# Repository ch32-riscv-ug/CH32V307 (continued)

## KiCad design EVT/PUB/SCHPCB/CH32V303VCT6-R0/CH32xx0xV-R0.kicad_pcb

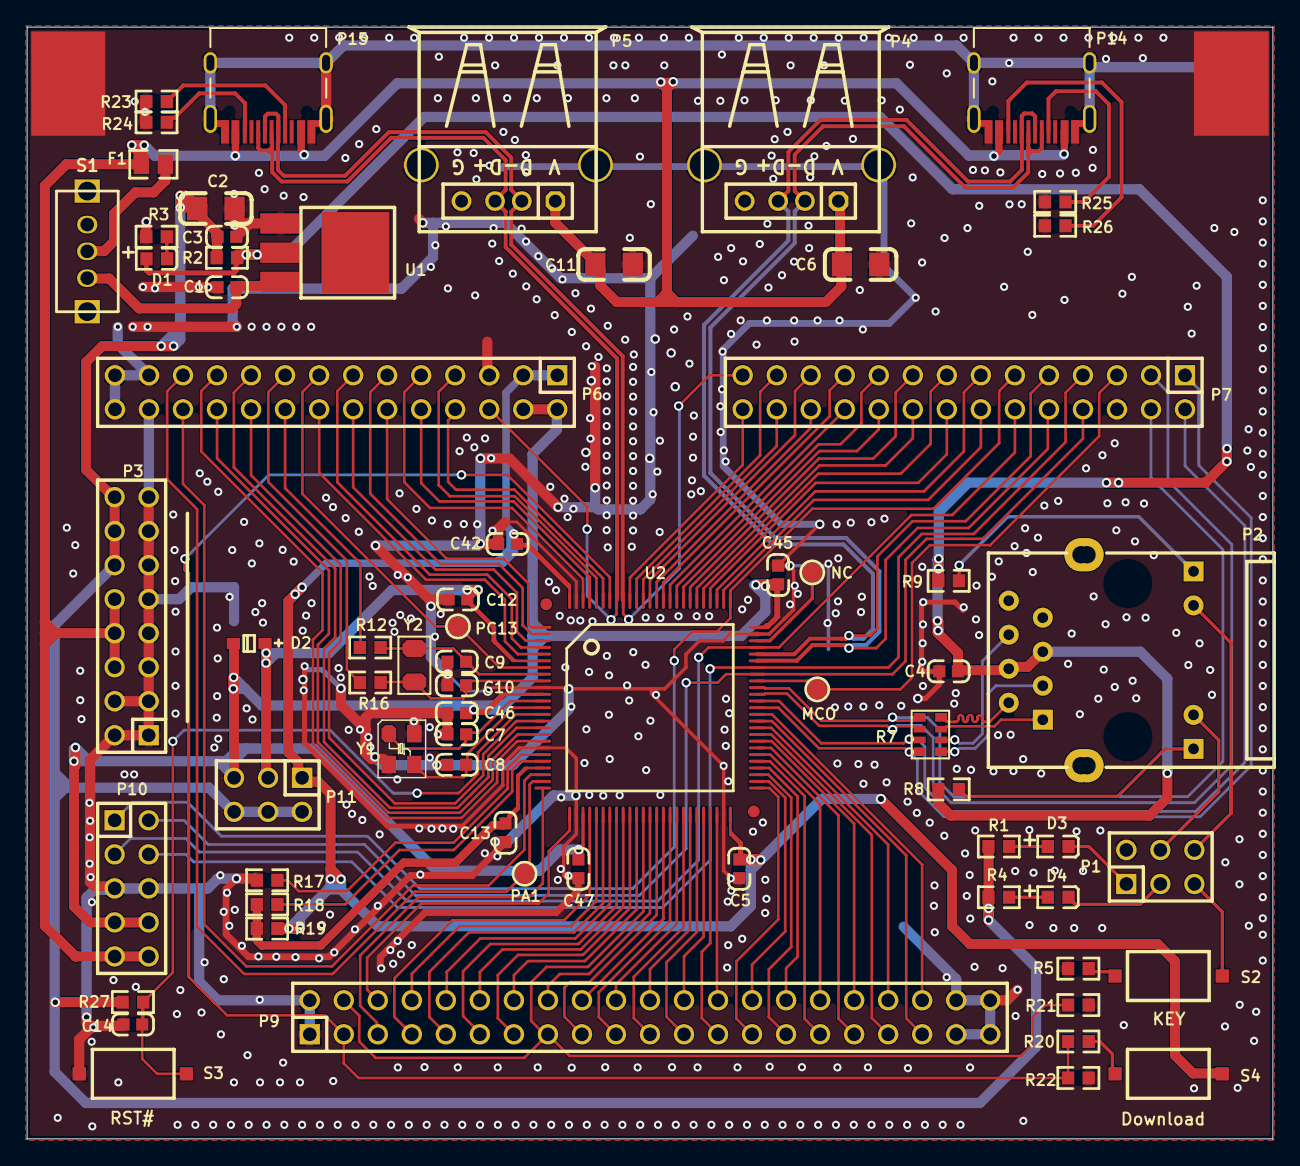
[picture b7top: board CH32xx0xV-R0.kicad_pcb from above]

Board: 2 copper layers, 93.0 x 83.0 mm, 68 parts (0 on the bottom side), 119 nets.

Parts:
C1, C3, C5, C12, C13, C14, C42, C45, C46, C47: 0.1uF; 0603_C
C2, C6, C11: 10uF; 3216_C
C4: 1uF; 0603_C
C7, C8: 22pF; 0603_C
C9, C10: 12pF; 0603_C
D1, D4: RED; 0603+
D2: B0520WS; SOD-323
D3: BLUE; 0603+
F1: 500mA; 0805
MCO: Testpoint; TESTPOINT1
NC: Testpoint; TESTPOINT1
P1: IO; IDC6-2.54mm
P2: HR911105A
P3: HEADER 8x2; IDC16-2.54mm
P4: USBFS; USBAF
P5: USBHS; USBAF
P6, P7: HEADER 14x2; IDC28-2.54MM
P9: HEADER 21x2; IDC42-2.54MM
P10: LINK; IDC10-2.54mm
P11: HEADER 3x2; IDC6-2.54mm
P14: USBFS; TYPE-C-Receptacle-2.0
P15: USBHS; TYPE-C-Receptacle-2.0
PA1: Testpoint; TESTPOINT1
PC13: Testpoint; TESTPOINT1
R1, R3, R4, R8, R9, R20: 1K; 0603
R2, R17, R18, R19: 0R; 0603
R5, R21, R22, R27: 10K; 0603
R7: 0Ω; RCA-8P4R-0603
R12, R16: NC(0R); 0603
R23: NC(5.1K); 0603
R24, R25, R26: 5.1K; 0603
S1: SW SPDT; KEY2
S2: KEY; SMD_6.1x3.65x2.5mm-KEY
S3: RST#; SMD_6.1x3.65x2.5mm-KEY
S4: Download; SMD_6.1x3.65x2.5mm-KEY
U1: 1117-3.3V; SOT-223
U2: CH32F207V; LQFP100
Y1: 8MHz; XT3225
Y2: 32768Hz; FC-135

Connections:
3V3: C2.1, C3.1, P3.12, P3.14, P3.16, P11.2, P11.4, P11.6, R1.1, R2.1, R4.1, R27.2
3V3S: C4.2, D1.1, P2.4, P2.5, R2.2, R8.1, R9.1, U1.2
5V: C6.1, C11.1, F1.1, P3.6, P3.8, P3.10, P4.1, P5.1, P10.9, P10.10, P14.A4, P14.B4, P15.A4, P15.B4
BOOT0: P9.3, R20.1, R22.1, U2.94
BOOT1: P9.4, P9.15, R21.1, U2.37
ELED1: P1.4, P2.10
ELED2: P1.6, P2.11
ERXN: P7.2, R7.3, U2.64
ERXN1: P2.6, R7.6
ERXP: P7.1, R7.4, U2.63
ERXP1: P2.3, R7.5
ETXN: P7.4, R7.1, U2.66
ETXN1: P2.2, R7.8
ETXP: P7.3, R7.2, U2.65
ETXP1: P2.1, R7.7
GND: C1.2, C2.2, C3.2, C4.1, C5.2, C6.2, C7.1, C8.1, C9.1, C10.1, C11.2, C12.1, C13.2, C14.1, C42.1, C45.2, C46.2, C47.1, P1.2, P2.8, P3.1, P3.2, P3.3, P3.4, P3.5, P3.7, P3.9, P3.11, P3.13, P3.15, P4.0, P4.4, P5.0, P5.4, P6.5, P6.25, P6.26, P6.27, P6.28, P7.6, P9.1, P9.2, P9.39, P9.40, P9.41, P9.42, P10.5, P10.6, P14.0, P14.A1, P14.B1, P15.0, P15.A1, P15.B1, R3.2, R5.1, R17.1, R21.2, R22.2, R23.2, R24.2, R25.2, R26.2, S3.1, U1.1, U2.10, U2.19, U2.27, U2.49, U2.74, U2.99, Y1.2, Y1.4
KEY: P1.5, S2.1
LED1: D3.2, P1.1
LED2: D4.2, P1.3
MCO: MCO.1, P7.5, U2.67
NC: NC.1, U2.73
NRST: C14.2, R27.1, S3.2, U2.14
NetC1_1: C1.1, S1.2, U1.3
NetD1_2: D1.2, R3.1
NetD3_1: D3.1, R1.2
NetD4_1: D4.1, R4.2
NetF1_2: F1.2, S1.1
NetP2_9: P2.9, R8.2
NetP2_12: P2.12, R9.2
NetP14_A5: P14.A5, R25.1
NetP14_B5: P14.B5, R26.1
NetP15_A5: P15.A5, R23.1
NetP15_B5: P15.B5, R24.1
NetR5_2: R5.2, S2.2
NetR20_2: R20.2, S4.2
PA0: P6.24, U2.23
PA1: P6.23, PA1.1, U2.24
PA2: P9.5, U2.25
PA3: P9.6, U2.26
PA4: P9.7, U2.29
PA5: P9.8, U2.30
PA6: P9.9, U2.31
PA7: P9.10, U2.32
PA9: P7.8, P10.2, U2.68
PA10: P7.7, P10.4, U2.69
PA11: P4.2, P7.10, P14.A7, P14.B7, U2.70
PA12: P4.3, P7.9, P14.A6, P14.B6, U2.71
PA13: P7.12, P10.3, U2.72
PA14: P7.11, P10.1, U2.76
PA15: P7.14, U2.77
PB0: P9.13, U2.35
PB1: P9.14, U2.36
PB3: P7.26, U2.89
PB4: P7.25, U2.90
PB5: P7.28, U2.91
PB6: P5.2, P7.27, P15.A7, P15.B7, U2.92
PB7: P5.3, P6.6, P15.A6, P15.B6, U2.93
PB8: P6.8, U2.95
PB9: P6.7, U2.96
PB10: P9.25, U2.47
PB11: P9.26, U2.48
PB12: P9.27, U2.51
PB13: P9.28, U2.52
PB14: P9.29, U2.53
PB15: P9.30, U2.54
PC0: P6.20, U2.15
PC1: P6.19, U2.16
PC2: P6.22, U2.17
PC3: P6.21, U2.18
PC4: P9.11, U2.33
PC5: P9.12, U2.34
PC10: P7.13, U2.78
PC11: P7.16, U2.79
PC12: P7.15, U2.80
PC13: P6.15, PC13.1, U2.7
PC14: P6.18, R12.1
PC15: P6.17, R16.1
PD0: P7.18, U2.81
PD1: P7.17, U2.82
PD2: P7.20, U2.83
PD3: P7.19, U2.84
PD4: P7.22, U2.85
PD5: P7.21, U2.86
PD6: P7.24, U2.87
PD7: P7.23, U2.88
PD8: P9.31, U2.55
PD9: P9.32, U2.56
PD10: P9.33, U2.57
PD11: P9.34, U2.58
PD12: P9.35, U2.59
PD13: P9.36, U2.60
PD14: P9.37, U2.61
PD15: P9.38, U2.62
PE0: P6.10, U2.97
PE1: P6.9, U2.98
PE2: P6.12, U2.1
PE3: P6.11, U2.2
PE4: P6.14, U2.3
PE5: P6.13, U2.4
PE6: P6.16, U2.5
PE7: P9.16, U2.38
PE8: P9.17, U2.39
PE9: P9.18, U2.40
PE10: P9.19, U2.41
PE11: P9.20, U2.42
PE12: P9.21, U2.43
PE13: P9.22, U2.44
PE14: P9.23, U2.45
PE15: P9.24, U2.46
VBAT: C12.2, D2.1, P11.3, U2.6
VDD: C45.1, C46.1, C47.2, D2.2, P6.2, P6.4, P10.7, P10.8, P11.5, U2.11, U2.28, U2.75
VDDA: C13.1, R18.1, R19.2, U2.22
VIO: C5.1, C42.2, P6.1, P6.3, P11.1, R19.1, S4.1, U2.50, U2.100
VREF+: R18.2, U2.21
VREF-: R17.2, U2.20
X32KI: C9.2, R12.2, U2.8, Y2.1
X32KO: C10.2, R16.2, U2.9, Y2.2
XI: C7.2, U2.12, Y1.1
XO: C8.2, U2.13, Y1.3

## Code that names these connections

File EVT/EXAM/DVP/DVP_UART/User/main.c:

/********************************** (C) COPYRIGHT *******************************
* File Name          : main.c
* Author             : WCH
* Version            : V1.0.0
* Date               : 2024/03/05
* Description        : Main program body.
*********************************************************************************
* Copyright (c) 2021 Nanjing Qinheng Microelectronics Co., Ltd.
* Attention: This software (modified or not) and binary are used for 
* microcontroller manufactured by Nanjing Qinheng Microelectronics.
*******************************************************************************/
#include "debug.h"
#include "ov.h"

/*
 *@Note
  DVP routine to operate OV2640 camera JPEG mode:
    Output picture data through UART2 (PA2), display pictures through serial port image software,
    or take 0xFF from a frame of data, starting with 0xD8;0xFF, data at the end of 0xD9, modify the
    file format to display pictures.
  DVP--PIN:
    D10--PD6
    D11--PD2
    D8--PC10
    D9--PC12
    DPWDN--PC3
    DPCLK--PA6
    D7--PB9
    D6--PB8
    D5--PB6
    D4--PC11
    D3--PC9
    D2--PC8
    D1--PA10
    D0--PA9
    RESET--PC13
    SDA--PB11
    HERF--PA4
    SDCLK--PB10
    SYNC--PA5

    Use UART2 (PA2) serial port output, #define DEBUG DEBUG_UART2 in debug.h
    UART1(PA9) is occupied by DVP
 */


/* DVP Work Mode */
#define JPEG_MODE     1
/* DVP Work Mode Selection */
#define DVP_Work_Mode    JPEG_MODE


UINT32  JPEG_DVPDMAaddr0 = 0x20005000;
UINT32  JPEG_DVPDMAaddr1 = 0x20005000 + OV2640_JPEG_WIDTH;

UINT32  RGB565_DVPDMAaddr0 = 0x20005000;
UINT32  RGB565_DVPDMAaddr1 = 0x20005000 + RGB565_COL_NUM;

volatile UINT32 frame_cnt = 0;
volatile UINT32 addr_cnt = 0;
volatile UINT32 href_cnt = 0;

void DVP_IRQHandler (void) __attribute__((interrupt("WCH-Interrupt-fast")));

/*********************************************************************
 * @fn      UART2_Send_Byte
 *
 * @brief   UART2 send one byte data.
 *
 * @param   t - UART send Data.
 *
 * @return  none
 */
void UART2_Send_Byte(u8 t)
{
    while (USART_GetFlagStatus(USART2, USART_FLAG_TC) == RESET);
    USART_SendData(USART2, t);
}

/*********************************************************************
 * @fn      DVP_Init
 *
 * @brief   Init DVP
 *
 * @return  none
 */
void DVP_Init(void)
{
    NVIC_InitTypeDef NVIC_InitStructure={0};

    RCC_AHBPeriphClockCmd(RCC_AHBPeriph_DVP, ENABLE);

    DVP->CR0 &= ~RB_DVP_MSK_DAT_MOD;

#if (DVP_Work_Mode == JPEG_MODE)
    /* VSYNC��HSYNC - High level active */
    DVP->CR0 |= RB_DVP_D8_MOD | RB_DVP_V_POLAR | RB_DVP_JPEG;
    DVP->CR1 &= ~(RB_DVP_ALL_CLR| RB_DVP_RCV_CLR);

    DVP->COL_NUM = OV2640_JPEG_WIDTH;

    DVP->DMA_BUF0 = JPEG_DVPDMAaddr0;        //DMA addr0
    DVP->DMA_BUF1 = JPEG_DVPDMAaddr1;        //DMA addr1
#endif

    /* Set frame capture rate */
    DVP->CR1 &= ~RB_DVP_FCRC;
    DVP->CR1 |= DVP_RATE_25P;  //25%

    /* Interupt Enable */
    DVP->IER |= RB_DVP_IE_STP_FRM;
    DVP->IER |= RB_DVP_IE_FIFO_OV;
    DVP->IER |= RB_DVP_IE_FRM_DONE;
    DVP->IER |= RB_DVP_IE_ROW_DONE;
    DVP->IER |= RB_DVP_IE_STR_FRM;

    NVIC_InitStructure.NVIC_IRQChannel = DVP_IRQn;
    NVIC_InitStructure.NVIC_IRQChannelPreemptionPriority = 0;
    NVIC_InitStructure.NVIC_IRQChannelSubPriority = 0;
    NVIC_InitStructure.NVIC_IRQChannelCmd = ENABLE;
    NVIC_Init(&NVIC_InitStructure);

    DVP->CR1 |= RB_DVP_DMA_EN;  //enable DMA
    DVP->CR0 |= RB_DVP_ENABLE;  //enable DVP
}

u32 DVP_ROW_cnt=0;

/*********************************************************************
 * @fn      DVP_IRQHandler
 *
 * @brief   This function handles DVP exception.
 *
 * @return  none
 */
void DVP_IRQHandler(void)
{
    if (DVP->IFR & RB_DVP_IF_ROW_DONE)
    {
        /* Write 0 clear 0 */
        DVP->IFR &= ~RB_DVP_IF_ROW_DONE;  //clear Interrupt

#if (DVP_Work_Mode == JPEG_MODE)
        href_cnt++;

        if (addr_cnt%2)     //buf1 done
        {
            addr_cnt++;
            DVP->DMA_BUF1 += OV2640_JPEG_WIDTH *2;
        }
        else                //buf0 done
        {
            addr_cnt++;
            DVP->DMA_BUF0 += OV2640_JPEG_WIDTH *2;
        }

#endif

    }

    if (DVP->IFR & RB_DVP_IF_FRM_DONE)
    {
        DVP->IFR &= ~RB_DVP_IF_FRM_DONE;  //clear Interrupt

#if (DVP_Work_Mode == JPEG_MODE)
        DVP->CR0 &= ~RB_DVP_ENABLE;       //disable DVP

        /* Use uart2 send JPEG data */
        {
            UINT32 i;
            UINT8 val;

            href_cnt = href_cnt*OV2640_JPEG_WIDTH;

            for(i=0; i<href_cnt; i++){
                val = *(UINT8*)(0x20005000+i);
                UART2_Send_Byte(val);
            }
        }

        DVP->CR0 |= RB_DVP_ENABLE;  //enable DVP

        DVP->DMA_BUF0 = JPEG_DVPDMAaddr0;        //DMA addr0
        DVP->DMA_BUF1 = JPEG_DVPDMAaddr1;        //DMA addr1
        href_cnt = 0;

        addr_cnt =0;

#endif

    }

    if (DVP->IFR & RB_DVP_IF_STR_FRM)
    {
        DVP->IFR &= ~RB_DVP_IF_STR_FRM;  //clear Interrupt

        frame_cnt++;
    }

    if (DVP->IFR & RB_DVP_IF_STP_FRM)
    {
        DVP->IFR &= ~RB_DVP_IF_STP_FRM;  //clear Interrupt

    }

    if (DVP->IFR & RB_DVP_IF_FIFO_OV)
    {
        DVP->IFR &= ~RB_DVP_IF_FIFO_OV;   //clear Interrupt

#if 0
        printf("FIFO OV\r\n");

#endif
    }

}

/*********************************************************************
 * @fn      main
 *
 * @brief   Main program.
 *
 * @return  none
 */
int main(void)
{
    NVIC_PriorityGroupConfig(NVIC_PriorityGroup_2);
	SystemCoreClockUpdate();
	Delay_Init();
	USART_Printf_Init(921600);	
	printf("SystemClk:%d\r\n",SystemCoreClock);
	printf( "ChipID:%08x\r\n", DBGMCU_GetCHIPID() );
    while(OV2640_Init())
    {
        printf("Camera Model Err\r\n");
        Delay_Ms(1000);
    }

    Delay_Ms(1000);

    RGB565_Mode_Init();
    Delay_Ms(1000);

#if (DVP_Work_Mode == JPEG_MODE)
    printf("JPEG_MODE\r\n");
    JPEG_Mode_Init();
    Delay_Ms(1000);

#endif

    DVP_Init();

    while(1);
}

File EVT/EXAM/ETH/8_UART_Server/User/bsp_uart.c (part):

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 *
 *  @brief   initialize uart1~uart8 io
 *
 *           UART1  TX-->PA9   RX-->PA10
 *           UART2  TX-->PA2   RX-->PA3
 *           UART3  TX-->PB10  RX-->PB11
 *           UART4  TX-->PC10  RX-->PC11
 *           UART5  TX-->PC12  RX-->PD2
 *           UART6  TX-->PC0   RX-->PC1   |  TX_2-->PE10   RX_2-->PE11
 *           UART7  TX-->PC2   RX-->PC3
 *           UART8  TX-->PC4   RX-->PC5
 *
 *  @param   none
 *
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    		               RCC_APB2Periph_GPIOC|RCC_APB2Periph_GPIOD|RCC_APB2Periph_GPIOE, ENABLE);

#ifndef CH32V307_DEBUG
    /* UART1 TX-->PA9   RX-->PA10 */
	GPIO_InitStructure.GPIO_Pin = GPIO_Pin_9;
	GPIO_InitStructure.GPIO_Speed = GPIO_Speed_50MHz;
	GPIO_InitStructure.GPIO_Mode = GPIO_Mode_AF_PP;
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	GPIO_Init(GPIOA, &GPIO_InitStructure);
#endif

    /* UART2 TX-->PA2   RX-->PA3 */
    GPIO_InitStructure.GPIO_Pin = GPIO_Pin_2;
    GPIO_InitStructure.GPIO_Speed = GPIO_Speed_50MHz;
    GPIO_InitStructure.GPIO_Mode = GPIO_Mode_AF_PP;
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    GPIO_Init(GPIOA, &GPIO_InitStructure);


    /* UART3 TX-->PB10  RX-->PB11 */
	GPIO_InitStructure.GPIO_Pin = GPIO_Pin_10;
	GPIO_InitStructure.GPIO_Speed = GPIO_Speed_50MHz;
	GPIO_InitStructure.GPIO_Mode = GPIO_Mode_AF_PP;
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	GPIO_InitStructure.GPIO_Mode = GPIO_Mode_IN_FLOATING;
	GPIO_Init(GPIOB, &GPIO_InitStructure);

	/* UART4 TX-->PC10  RX-->PC11 */
	GPIO_InitStructure.GPIO_Pin = GPIO_Pin_10;
	GPIO_InitStructure.GPIO_Speed = GPIO_Speed_50MHz;
	GPIO_InitStructure.GPIO_Mode = GPIO_Mode_AF_PP;
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	GPIO_InitStructure.GPIO_Mode = GPIO_Mode_IN_FLOATING;
	GPIO_Init(GPIOC, &GPIO_InitStructure);

	/* UART5 TX-->PC12  RX-->PD2 */
	GPIO_InitStructure.GPIO_Pin = GPIO_Pin_12;
	GPIO_InitStructure.GPIO_Speed = GPIO_Speed_50MHz;
	GPIO_InitStructure.GPIO_Mode = GPIO_Mode_AF_PP;
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	GPIO_InitStructure.GPIO_Mode = GPIO_Mode_IN_FLOATING;
	GPIO_Init(GPIOD, &GPIO_InitStructure);

	/* UART6 TX-->PC0  RX-->PC1  |  TX_2-->PE10   RX_2-->PE11 */
//	GPIO_InitStructure.GPIO_Pin = GPIO_Pin_0;
//	GPIO_InitStructure.GPIO_Speed = GPIO_Speed_50MHz;
//	GPIO_InitStructure.GPIO_Mode = GPIO_Mode_AF_PP;
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
    GPIO_PinRemapConfig(GPIO_FullRemap_USART6,ENABLE);

	/* UART7 TX-->PC2  RX-->PC3 */
	GPIO_InitStructure.GPIO_Pin = GPIO_Pin_2;
	GPIO_InitStructure.GPIO_Speed = GPIO_Speed_50MHz;
	GPIO_InitStructure.GPIO_Mode = GPIO_Mode_AF_PP;
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	GPIO_InitStructure.GPIO_Mode = GPIO_Mode_IN_FLOATING;
	GPIO_Init(GPIOC, &GPIO_InitStructure);

	/* UART8 TX-->PC4  RX-->PC5 */
	GPIO_InitStructure.GPIO_Pin = GPIO_Pin_4;
	GPIO_InitStructure.GPIO_Speed = GPIO_Speed_50MHz;
	GPIO_InitStructure.GPIO_Mode = GPIO_Mode_AF_PP;
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	USART_InitTypeDef USART_InitStructure={0};

#ifndef CH32V307_DEBUG
	/* USART1 TX-->PA9   RX-->PA10 */
	uart_data_t[0].RX_buffer = &UART1_RX_DMA_DataBuf[0];
	uart_data_t[0].TX_buffer = &UART1_TX_DMA_DataBuf[0];
	uart_data_t[0].TX_data_length = &UART1_TX_Buf_Length[0];
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	USART_Cmd(USART1, ENABLE);
#endif

	/* USART2 TX-->PA2   RX-->PA3 */
	uart_data_t[1].RX_buffer = &UART2_RX_DMA_DataBuf[0];
	uart_data_t[1].TX_buffer = &UART2_TX_DMA_DataBuf[0];
	uart_data_t[1].TX_data_length = &UART2_TX_Buf_Length[0];
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	USART_Init(USART2, &USART_InitStructure);
	USART_Cmd(USART2, ENABLE);

	/* USART3 TX-->PB10  RX-->PB11 */
	uart_data_t[2].RX_buffer = &UART3_RX_DMA_DataBuf[0];
	uart_data_t[2].TX_buffer = &UART3_TX_DMA_DataBuf[0];
	uart_data_t[2].TX_data_length = &UART3_TX_Buf_Length[0];
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	USART_Cmd(USART3, ENABLE);


	/* USART4 TX-->PC10  RX-->PC11 */
	uart_data_t[3].RX_buffer = &UART4_RX_DMA_DataBuf[0];
	uart_data_t[3].TX_buffer = &UART4_TX_DMA_DataBuf[0];
	uart_data_t[3].TX_data_length = &UART4_TX_Buf_Length[0];
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    USART_Init(UART4, &USART_InitStructure);
    USART_Cmd(UART4, ENABLE);

	/* USART5 TX-->PC12  RX-->PD2 */
	uart_data_t[4].RX_buffer = &UART5_RX_DMA_DataBuf[0];
	uart_data_t[4].TX_buffer = &UART5_TX_DMA_DataBuf[0];
	uart_data_t[4].TX_data_length = &UART5_TX_Buf_Length[0];
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    USART_Init(UART5, &USART_InitStructure);
    USART_Cmd(UART5, ENABLE);

    /* UART6 TX_2-->PE10   RX_2-->PE11 */
	uart_data_t[5].RX_buffer = &UART6_RX_DMA_DataBuf[0];
	uart_data_t[5].TX_buffer = &UART6_TX_DMA_DataBuf[0];
	uart_data_t[5].TX_data_length = &UART6_TX_Buf_Length[0];
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    USART_Init(UART6, &USART_InitStructure);
    USART_Cmd(UART6, ENABLE);

	/* UART7  TX-->PC2   RX-->PC3 */
	uart_data_t[6].RX_buffer = &UART7_RX_DMA_DataBuf[0];
	uart_data_t[6].TX_buffer = &UART7_TX_DMA_DataBuf[0];
	uart_data_t[6].TX_data_length = &UART7_TX_Buf_Length[0];
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    USART_Cmd(UART7, ENABLE);


	/* UART8  TX-->PC4   RX-->PC5 */
	uart_data_t[7].RX_buffer = &UART8_RX_DMA_DataBuf[0];
	uart_data_t[7].TX_buffer = &UART8_TX_DMA_DataBuf[0];
	uart_data_t[7].TX_data_length = &UART8_TX_Buf_Length[0];
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
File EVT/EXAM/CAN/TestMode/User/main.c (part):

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/*
 *@Note
 *CAN test mode, including silent mode, loopback mode and loopback silent mode:
 *CAN1-CAN_Tx(PB9),CAN_Rx(PB8)
 *CAN2-CAN_Tx(PB13),CAN_Rx(PB12)
 *Standard_Frame: includes a 32bit filter mask bit pattern.
 *
 */
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
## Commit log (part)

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2026-06-15 update: enhance update script and add GitHub Actions workflow for automated datasheet downloads
2026-06-15 update: adjust cron schedule for update workflow and enhance download error handling in script
2026-06-15 refactor update job to simplify commit logic in GitHub Actions workflow
2026-06-16 update GitHub Actions schedule
2026-06-19 update GitHub Actions workflow to implement keepalive logic and remove unnecessary permissions
2026-06-19 refactor fetch function in update.sh to simplify error handling and remove retry logic
